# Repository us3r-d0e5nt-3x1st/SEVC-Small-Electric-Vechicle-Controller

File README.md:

# SEVC - Small Electric Vechicle Controller
A small and efficient ESC made for all kinds of EVs

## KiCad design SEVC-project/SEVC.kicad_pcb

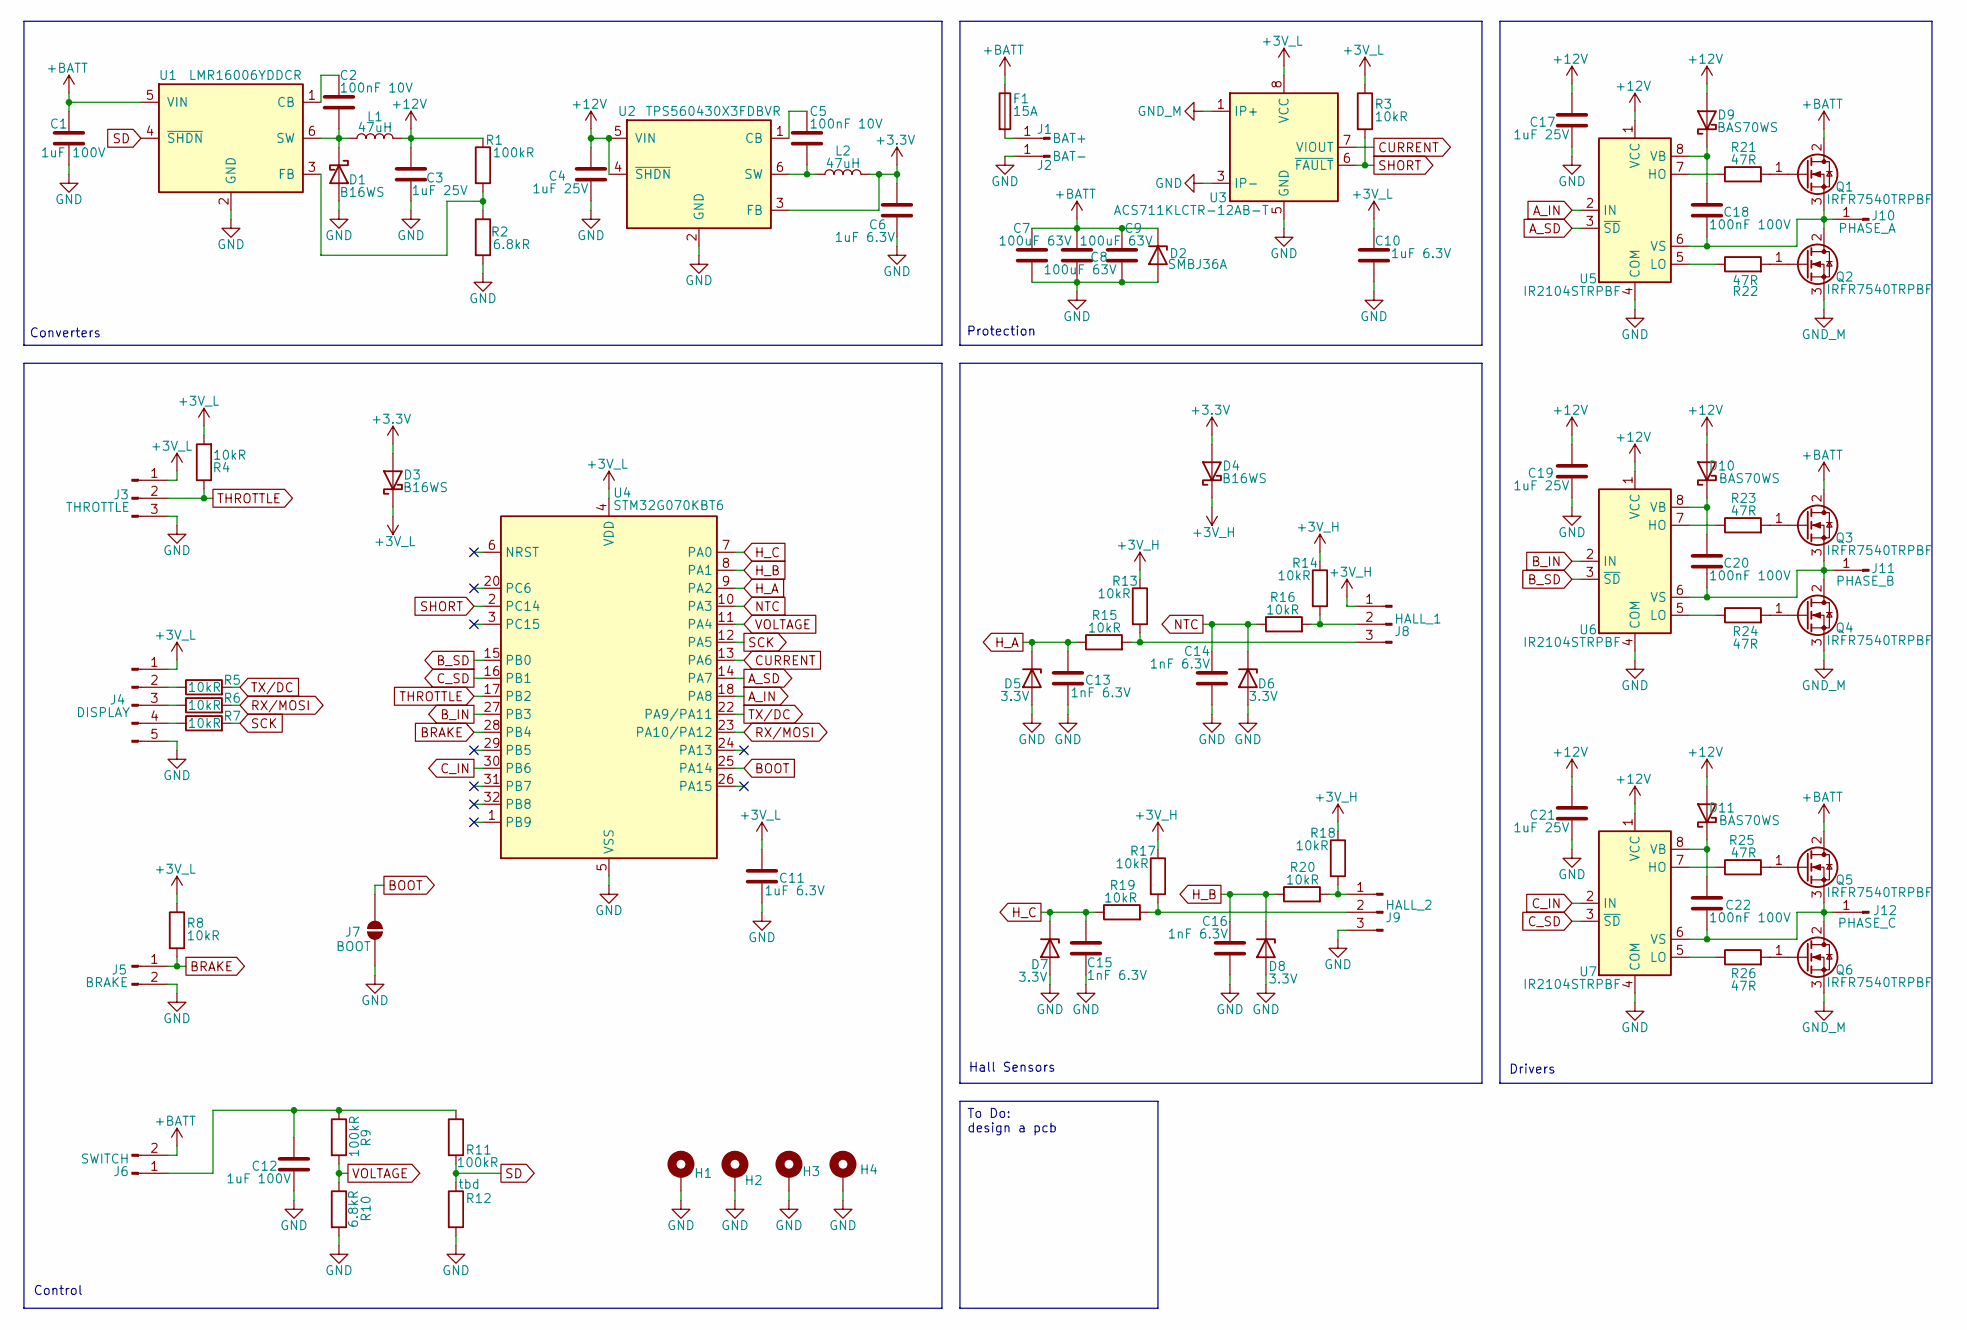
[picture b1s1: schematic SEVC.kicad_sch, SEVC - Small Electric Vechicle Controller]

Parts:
C1, C12: 1uF 100V; C_0805_2012Metric
C2, C5: 100nF 10V; C_0805_2012Metric
C3, C4, C17, C19, C21: 1uF 25V; C_0805_2012Metric
C6, C10, C11: 1uF 6.3V; C_0805_2012Metric
C7, C8, C9: 100uF 63V; C_Radial_D8.0mm_H11.5mm_P3.50mm
C13, C14, C15, C16: 1nF 6.3V; C_0805_2012Metric
C18, C20, C22: 100nF 100V; C_0805_2012Metric
D1, D3, D4: B16WS; D_SOD-323
D2: SMBJ36A; D_SMB
D5, D6, D7, D8: 3.3V; D_SOD-323
D9, D10, D11: BAS70WS; D_SOD-323
F1: 15A; Fuseholder_Littelfuse_Nano2_154x
H1, H2, H3, H4: MountingHole_Pad; MountingHole_2.2mm_M2_Pad_Via
J1: BAT+; SolderWire-4sqmm_1x01_D3mm_OD6mm
J2: BAT-; SolderWire-4sqmm_1x01_D3mm_OD6mm
J3: THROTTLE; PinHeader_1x03_P2.00mm_Vertical
J4: DISPLAY; PinHeader_1x05_P2.00mm_Vertical
J5: BRAKE; PinHeader_1x02_P2.00mm_Vertical
J6: SWITCH; PinHeader_1x02_P2.00mm_Vertical
J7: BOOT; SolderJumper-2_P1.3mm_Open_RoundedPad1.0x1.5mm
J8: HALL_1; PinHeader_1x03_P2.00mm_Vertical
J9: HALL_2; PinHeader_1x03_P2.00mm_Vertical
J10: PHASE_A; SolderWire-2sqmm_1x01_D2mm_OD3.9mm
J11: PHASE_B; SolderWire-2sqmm_1x01_D2mm_OD3.9mm
J12: PHASE_C; SolderWire-2sqmm_1x01_D2mm_OD3.9mm
L1, L2: 47uH; L_Cenker_CKCS3015
Q1, Q2, Q3, Q4, Q5, Q6: IRFR7540TRPBF; TO-252-2
R1, R9, R11: 100kR; R_0805_2012Metric
R2, R10: 6.8kR; R_0805_2012Metric
R3, R4, R5, R6, R7, R8, R13, R14, R15, R16, R17, R18, R19, R20: 10kR; R_0805_2012Metric
R12: tbd; R_0805_2012Metric
R21, R22, R23, R24, R25, R26: 47R; R_0805_2012Metric
U1: LMR16006YDDCR; SOT-23-6
U2: TPS560430X3FDBVR; SOT-23-6
U3: ACS711KLCTR-12AB-T; SOIC-8_3.9x4.9mm_P1.27mm
U4: STM32G070KBT6; LQFP-32_7x7mm_P0.8mm
U5, U6, U7: IR2104STRPBF; SOIC-8_3.9x4.9mm_P1.27mm

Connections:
+3.3V: C6.1, D3.2 (A), D4.2 (A), L2.2, U2.3 (FB)
+3V_H: D4.1 (K), J8.1, R13.1, R14.1, R17.1, R18.1
+3V_L: C10.1, C11.1, D3.1 (K), J3.1, J4.1, R3.1, R4.2, R8.1, U3.8 (VCC), U4.4 (VDD)
+12V: C3.1, C4.1, C17.1, C19.1, C21.1, D9.2 (A), D10.2 (A), D11.2 (A), L1.2, R1.1, U2.4 (~SHDN), U2.5 (VIN), U5.1 (VCC), U6.1 (VCC), U7.1 (VCC)
+BATT: C1.1, C7.1, C8.1, C9.1, D2.1 (K), F1.1, J6.2, Q1.2 (D), Q3.2 (D), Q5.2 (D), U1.5 (VIN)
A_IN: U4.18 (PA8), U5.2 (IN)
A_SD: U4.14 (PA7), U5.3 (~SD)
BOOT: J7.2 (B), U4.25 (PA14)
BRAKE: J5.1, R8.2, U4.28 (PB4)
B_IN: U4.27 (PB3), U6.2 (IN)
B_SD: U4.15 (PB0), U6.3 (~SD)
CURRENT: U3.7 (VIOUT), U4.13 (PA6)
C_IN: U4.30 (PB6), U7.2 (IN)
C_SD: U4.16 (PB1), U7.3 (~SD)
GND: C1.2, C3.2, C4.2, C6.2, C7.2, C8.2, C9.2, C10.2, C11.2, C12.2, C13.2, C14.2, C15.2, C16.2, C17.2, C19.2, C21.2, D1.2 (A), D2.2 (A), D5.2 (A), D6.2 (A), D7.2 (A), D8.2 (A), H1.1 (1_1), H2.1 (1_1), H3.1 (1_1), H4.1 (1_1), J2.1 (Pin_1_1), J3.3, J4.5, J5.2, J7.1 (A), J9.3, R2.2, R10.2, R12.2, U1.2 (GND), U2.2 (GND), U3.3 (IP-), U3.4 (IP-), U3.5 (GND), U4.5 (VSS), U5.4 (COM), U6.4 (COM), U7.4 (COM)
GND_M: Q2.3 (S), Q4.3 (S), Q6.3 (S), U3.1 (IP+), U3.2 (IP+)
H_A: C13.1, D5.1 (K), R15.1, U4.9 (PA2)
H_B: C16.1, D8.1 (K), R20.1, U4.8 (PA1)
H_C: C15.1, D7.1 (K), R19.1, U4.7 (PA0)
NTC: C14.1, D6.1 (K), R16.1, U4.10 (PA3)
unnamed: C2.2, D1.1 (K), L1.1, U1.6 (SW)
unnamed: C18.2, D9.1 (K), U5.8 (VB)
unnamed: C20.2, D10.1 (K), U6.8 (VB)
unnamed: C22.2, D11.1 (K), U7.8 (VB)
unnamed: F1.2, J1.1 (Pin_1_1)
unnamed: J4.2, R5.1
unnamed: J4.3, R6.1
unnamed: J4.4, R7.1
unnamed: C12.1, J6.1, R9.1, R11.1
unnamed: J8.2, R14.2, R16.2
unnamed: J8.3, R13.2, R15.2
unnamed: J9.1, R18.2, R20.2
unnamed: J9.2, R17.2, R19.2
unnamed: C18.1, J10.1 (Pin_1_1), Q1.3 (S), Q2.2 (D), U5.6 (VS)
unnamed: C20.1, J11.1 (Pin_1_1), Q3.3 (S), Q4.2 (D), U6.6 (VS)
unnamed: C22.1, J12.1 (Pin_1_1), Q5.3 (S), Q6.2 (D), U7.6 (VS)
unnamed: Q1.1 (G), R21.2
unnamed: Q2.1 (G), R22.2
unnamed: Q3.1 (G), R23.2
unnamed: Q4.1 (G), R24.2
unnamed: Q5.1 (G), R25.2
unnamed: Q6.1 (G), R26.2
unnamed: C2.1, U1.1 (CB)
unnamed: R1.2, R2.1, U1.3 (FB)
unnamed: C5.1, U2.1 (CB)
unnamed: C5.2, L2.1, U2.6 (SW)
unnamed: R21.1, U5.7 (HO)
unnamed: R22.1, U5.5 (LO)
unnamed: R23.1, U6.7 (HO)
unnamed: R24.1, U6.5 (LO)
unnamed: R25.1, U7.7 (HO)
unnamed: R26.1, U7.5 (LO)
RX/MOSI: R6.2, U4.23 (PA10/PA12)
SCK: R7.2, U4.12 (PA5)
SD: R11.2, R12.1, U1.4 (~SHDN)
SHORT: R3.2, U3.6 (~FAULT), U4.2 (PC14)
THROTTLE: J3.2, R4.1, U4.17 (PB2)
TX/DC: R5.2, U4.22 (PA9/PA11)
VOLTAGE: R9.2, R10.1, U4.11 (PA4)

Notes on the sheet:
Drivers
Control
Converters
Protection
Hall Sensors
To Do: design a pcb

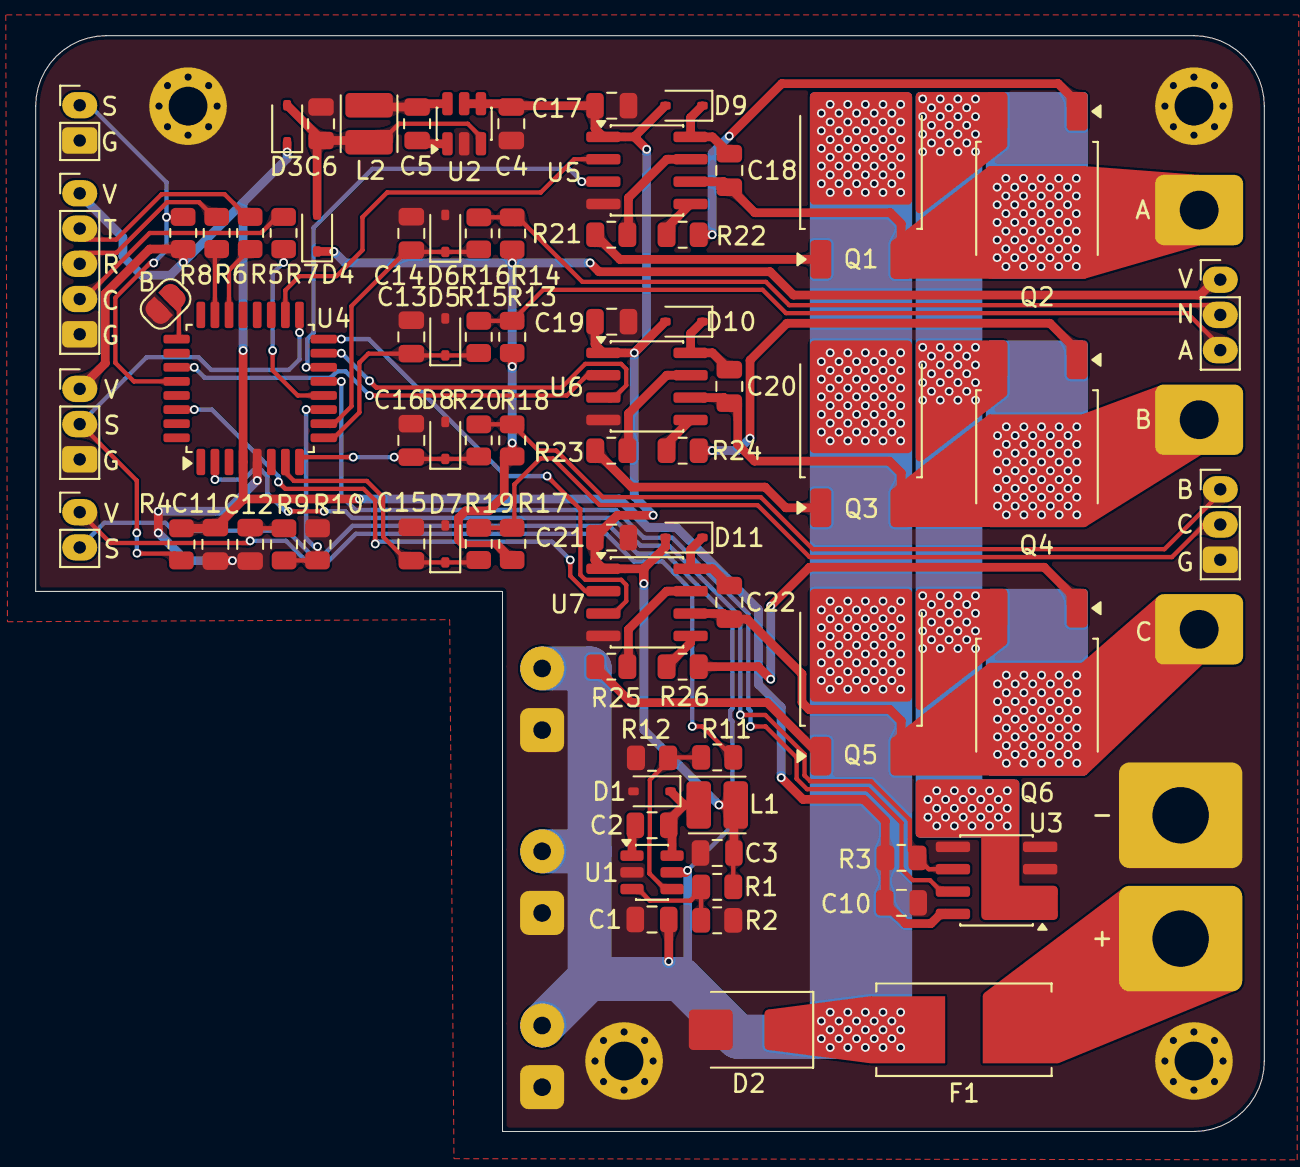
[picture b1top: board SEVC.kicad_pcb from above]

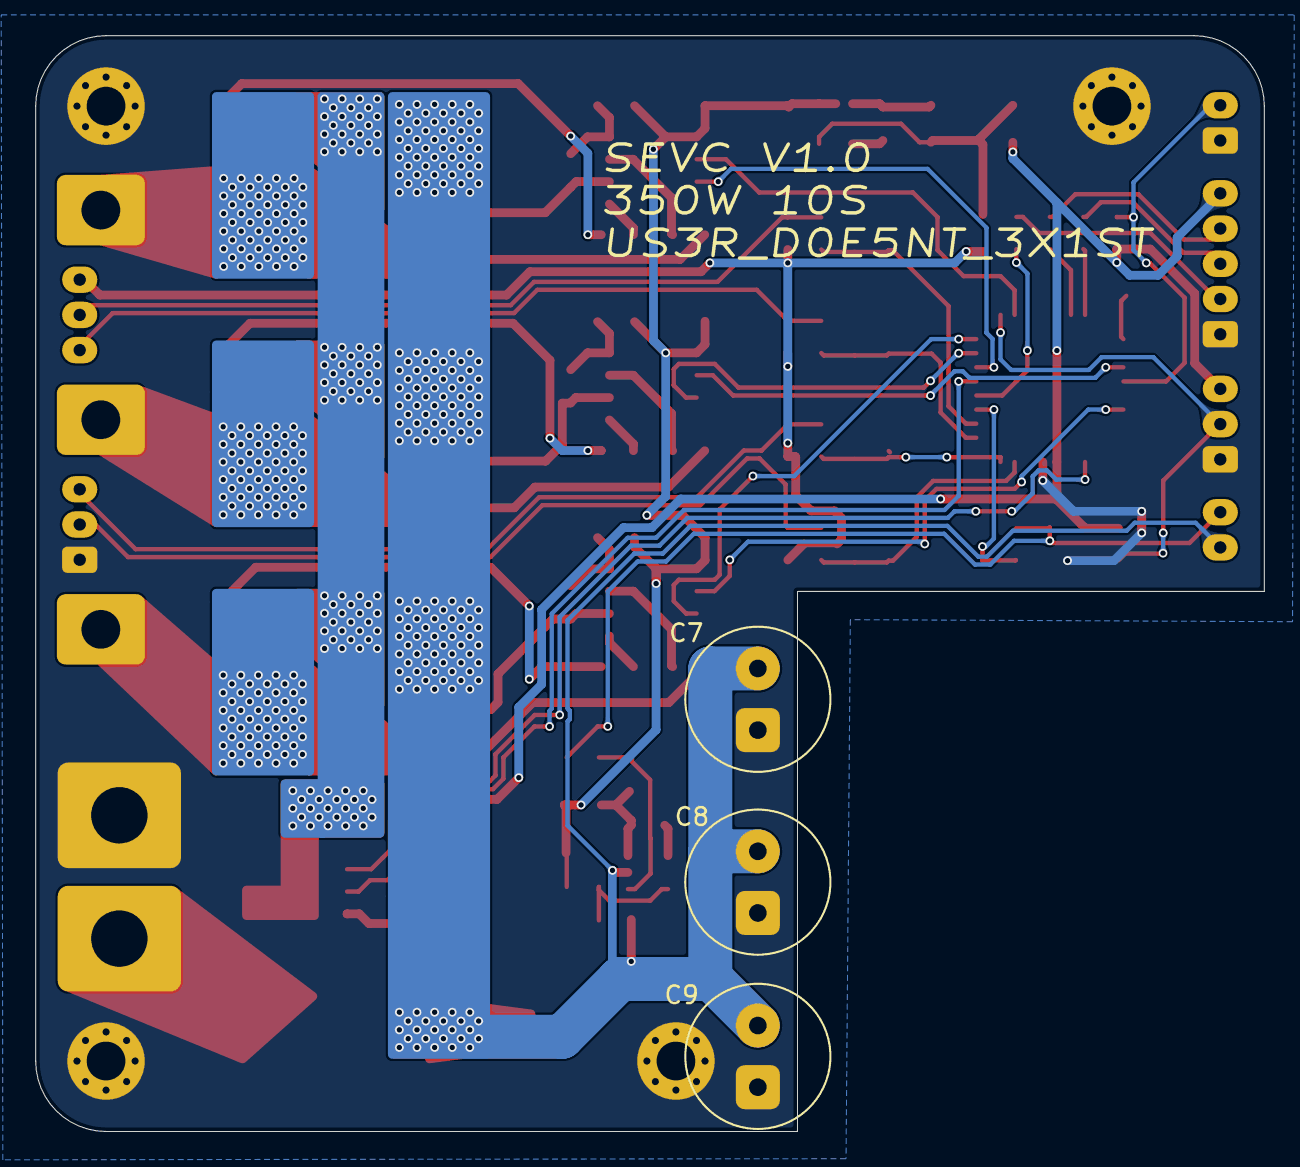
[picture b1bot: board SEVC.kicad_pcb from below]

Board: 2 copper layers, 69.7 x 62.2 mm, 91 parts (3 on the bottom side), 59 nets.

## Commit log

2026-05-29 Fix README title formatting and spelling
2026-05-29 Update issue templates
2026-05-29 Fix typo in README description
2026-05-29 Include PCB image in README
    Add image to README for visual reference
